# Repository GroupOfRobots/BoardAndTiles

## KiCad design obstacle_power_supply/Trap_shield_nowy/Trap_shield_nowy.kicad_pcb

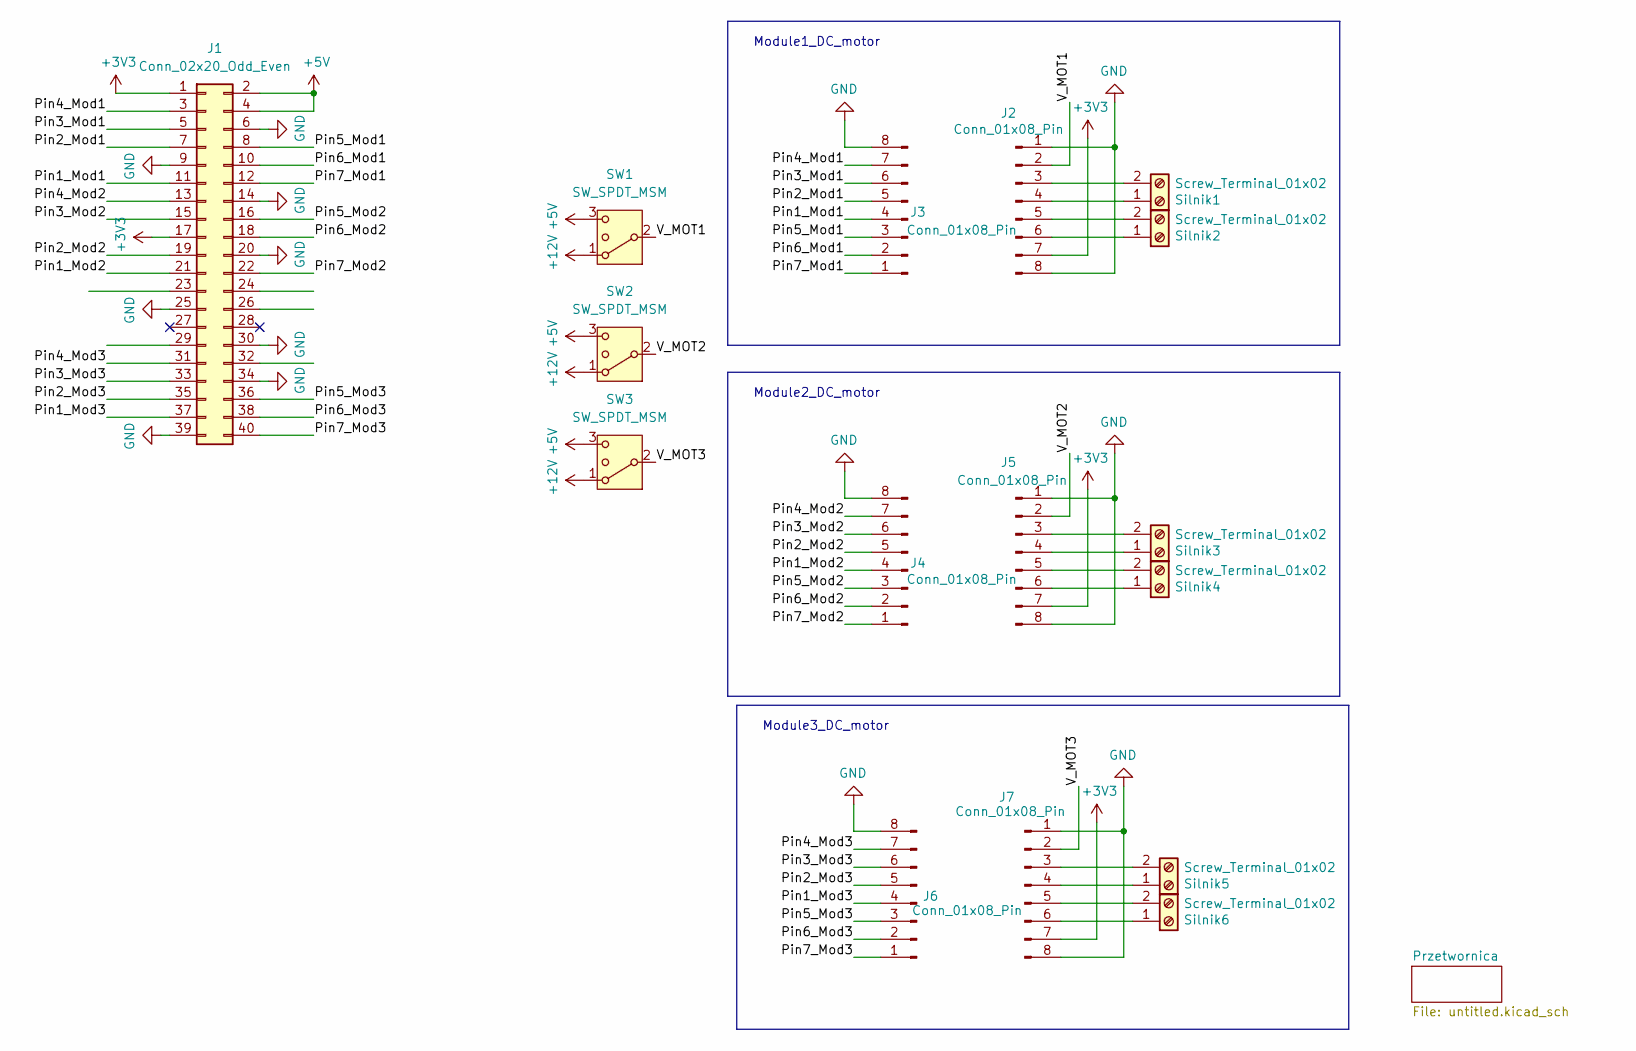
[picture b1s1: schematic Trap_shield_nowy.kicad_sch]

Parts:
J1: Conn_02x20_Odd_Even; PinHeader_2x20_P2.54mm_Vertical
J2, J3, J4, J5, J6, J7: Conn_01x08_Pin; PinSocket_1x08_P2.54mm_Vertical
SW1, SW2, SW3: SW_SPDT_MSM; SW_Slide-03_Wuerth-WS-SLTV_10x2.5x6.4_P2.54mm
Silnik1, Silnik2, Silnik3, Silnik4, Silnik5, Silnik6: Screw_Terminal_01x02; TerminalBlock_bornier-2_P5.08mm

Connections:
+3V3: J1.1, J1.17, J2.7, J5.7, J7.7
+5V: J1.2, J1.4, SW1.3 (4), SW2.3 (4), SW3.3 (4); also elsewhere on the board
+12V: SW1.1, SW2.1, SW3.1; also elsewhere on the board
/Pin1_Mod1: J1.11, J3.4
/Pin1_Mod2: J1.21, J4.4
/Pin1_Mod3: J1.37, J6.4
/Pin2_Mod1: J1.7, J3.5
/Pin2_Mod2: J1.19, J4.5
/Pin2_Mod3: J1.35, J6.5
/Pin3_Mod1: J1.5, J3.6
/Pin3_Mod2: J1.15, J4.6
/Pin3_Mod3: J1.33, J6.6
/Pin4_Mod1: J1.3, J3.7
/Pin4_Mod2: J1.13, J4.7
/Pin4_Mod3: J1.31, J6.7
/Pin5_Mod1: J1.8, J3.3
/Pin5_Mod2: J1.16, J4.3
/Pin5_Mod3: J1.36, J6.3
/Pin6_Mod1: J1.10, J3.2
/Pin6_Mod2: J1.18, J4.2
/Pin6_Mod3: J1.38, J6.2
/Pin7_Mod1: J1.12, J3.1
/Pin7_Mod2: J1.22, J4.1
/Pin7_Mod3: J1.40, J6.1
/V_MOT1: J2.2, SW1.2 (3)
/V_MOT2: J5.2, SW2.2 (3)
/V_MOT3: J7.2, SW3.2 (3)
GND: J1.6, J1.9, J1.14, J1.20, J1.25, J1.30, J1.34, J1.39, J2.1, J2.8, J3.8, J4.8, J5.1, J5.8, J6.8, J7.1, J7.8; also elsewhere on the board
unnamed: J2.3, Silnik1.2
unnamed: J2.4, Silnik1.1
unnamed: J2.5, Silnik2.2
unnamed: J2.6, Silnik2.1
unnamed: J5.3, Silnik3.2
unnamed: J5.4, Silnik3.1
unnamed: J5.5, Silnik4.2
unnamed: J5.6, Silnik4.1
unnamed: J7.3, Silnik5.2
unnamed: J7.4, Silnik5.1
unnamed: J7.5, Silnik6.2
unnamed: J7.6, Silnik6.1

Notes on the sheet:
Module2_DC_motor
Module1_DC_motor
Module3_DC_motor

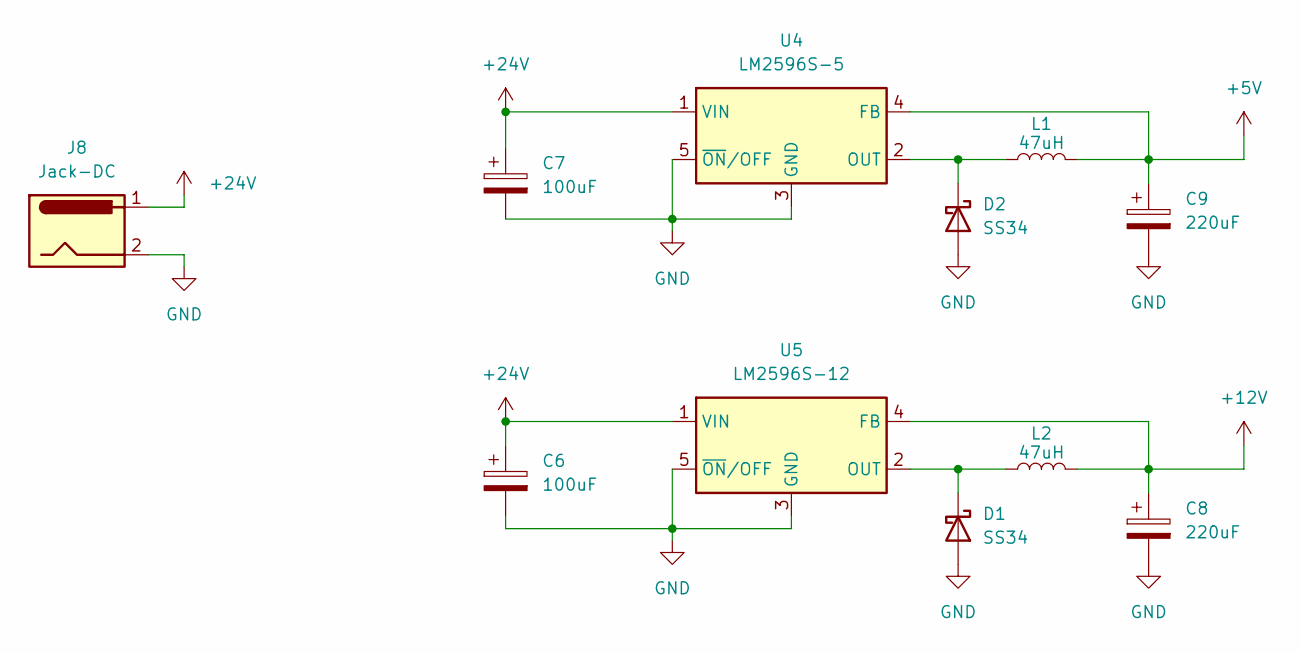
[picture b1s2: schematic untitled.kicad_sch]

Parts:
C6, C7: 100uF; C_Elec_8x10.2
C8, C9: 220uF; C_Elec_8x10.2
D1, D2: SS34; D_SMA_Handsoldering
J8: Jack-DC; BarrelJack_GCT_DCJ200-10-A_Horizontal
L1, L2: 47uH; L_12x12mm_H8mm
U4: LM2596S-5; TO-263-5_TabPin3
U5: LM2596S-12; TO-263-5_TabPin3

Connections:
+5V: C9.1, L1.2, U4.4 (FB); also elsewhere on the board
+12V: C8.1, L2.2, U5.4 (FB); also elsewhere on the board
+24V: C6.1, C7.1, J8.1, U4.1 (VIN), U5.1 (VIN)
GND: C6.2, C7.2, C8.2, C9.2, D1.2 (A), D2.2 (A), J8.2, J8.3, U4.3 (GND), U4.5 (~ON/OFF), U5.3 (GND), U5.5 (~ON/OFF); also elsewhere on the board
unnamed: D1.1 (K), L2.1, U5.2 (OUT)
unnamed: D2.1 (K), L1.1, U4.2 (OUT)

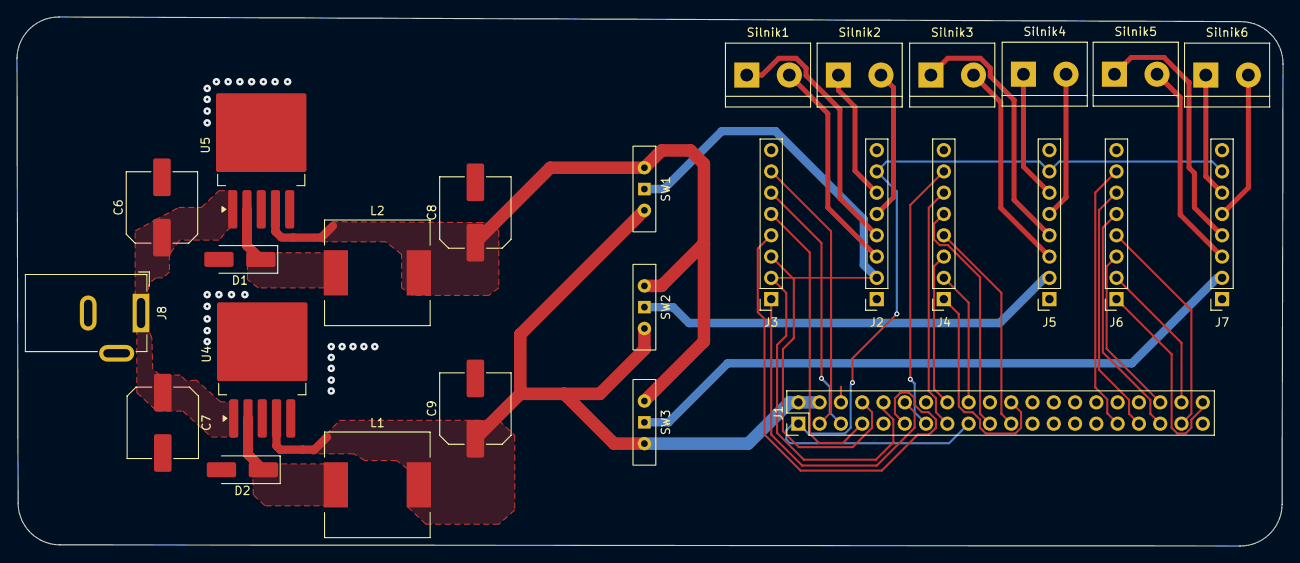
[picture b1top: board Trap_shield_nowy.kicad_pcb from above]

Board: 2 copper layers, 151.1 x 63.1 mm, 27 parts (0 on the bottom side), 43 nets.

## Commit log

2025-01-23 poszerzanie
2025-03-28 moving track support
2025-04-23 track support - bumper
2025-04-23 bump - stl
2025-05-19 tensioner added
2025-06-05 Adding schematic for multiple trap powering shield
2025-06-05 PDF with board pinout
